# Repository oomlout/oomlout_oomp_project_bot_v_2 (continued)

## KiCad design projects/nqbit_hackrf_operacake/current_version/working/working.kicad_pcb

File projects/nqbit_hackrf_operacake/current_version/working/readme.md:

# hackrf
 
## summary 
* id: nqbit_hackrf_operacake
* user: nqbit
* name: hackrf
* board: operacake
* repo: https://github.com/nqbit/hackrf
* src_file_repo_kicad_pcb: hardware/operacake/operacake.kicad_pcb
* src_file_repo_kicad_pcb_link: https://github.com/nqbit/hackrf/tree/master/hardware/operacake/operacake.kicad_pcb

* src_file_repo_sch: hardware/operacake/operacake.sch
* src_file_repo_sch_link: https://github.com/nqbit/hackrf/tree/master/hardware/operacake/operacake.sch
* full details link: https://github.com/oomlout/oomlout_oomp_project_bot_v_2/tree/main/projects/nqbit_hackrf_operacake/current_version/working

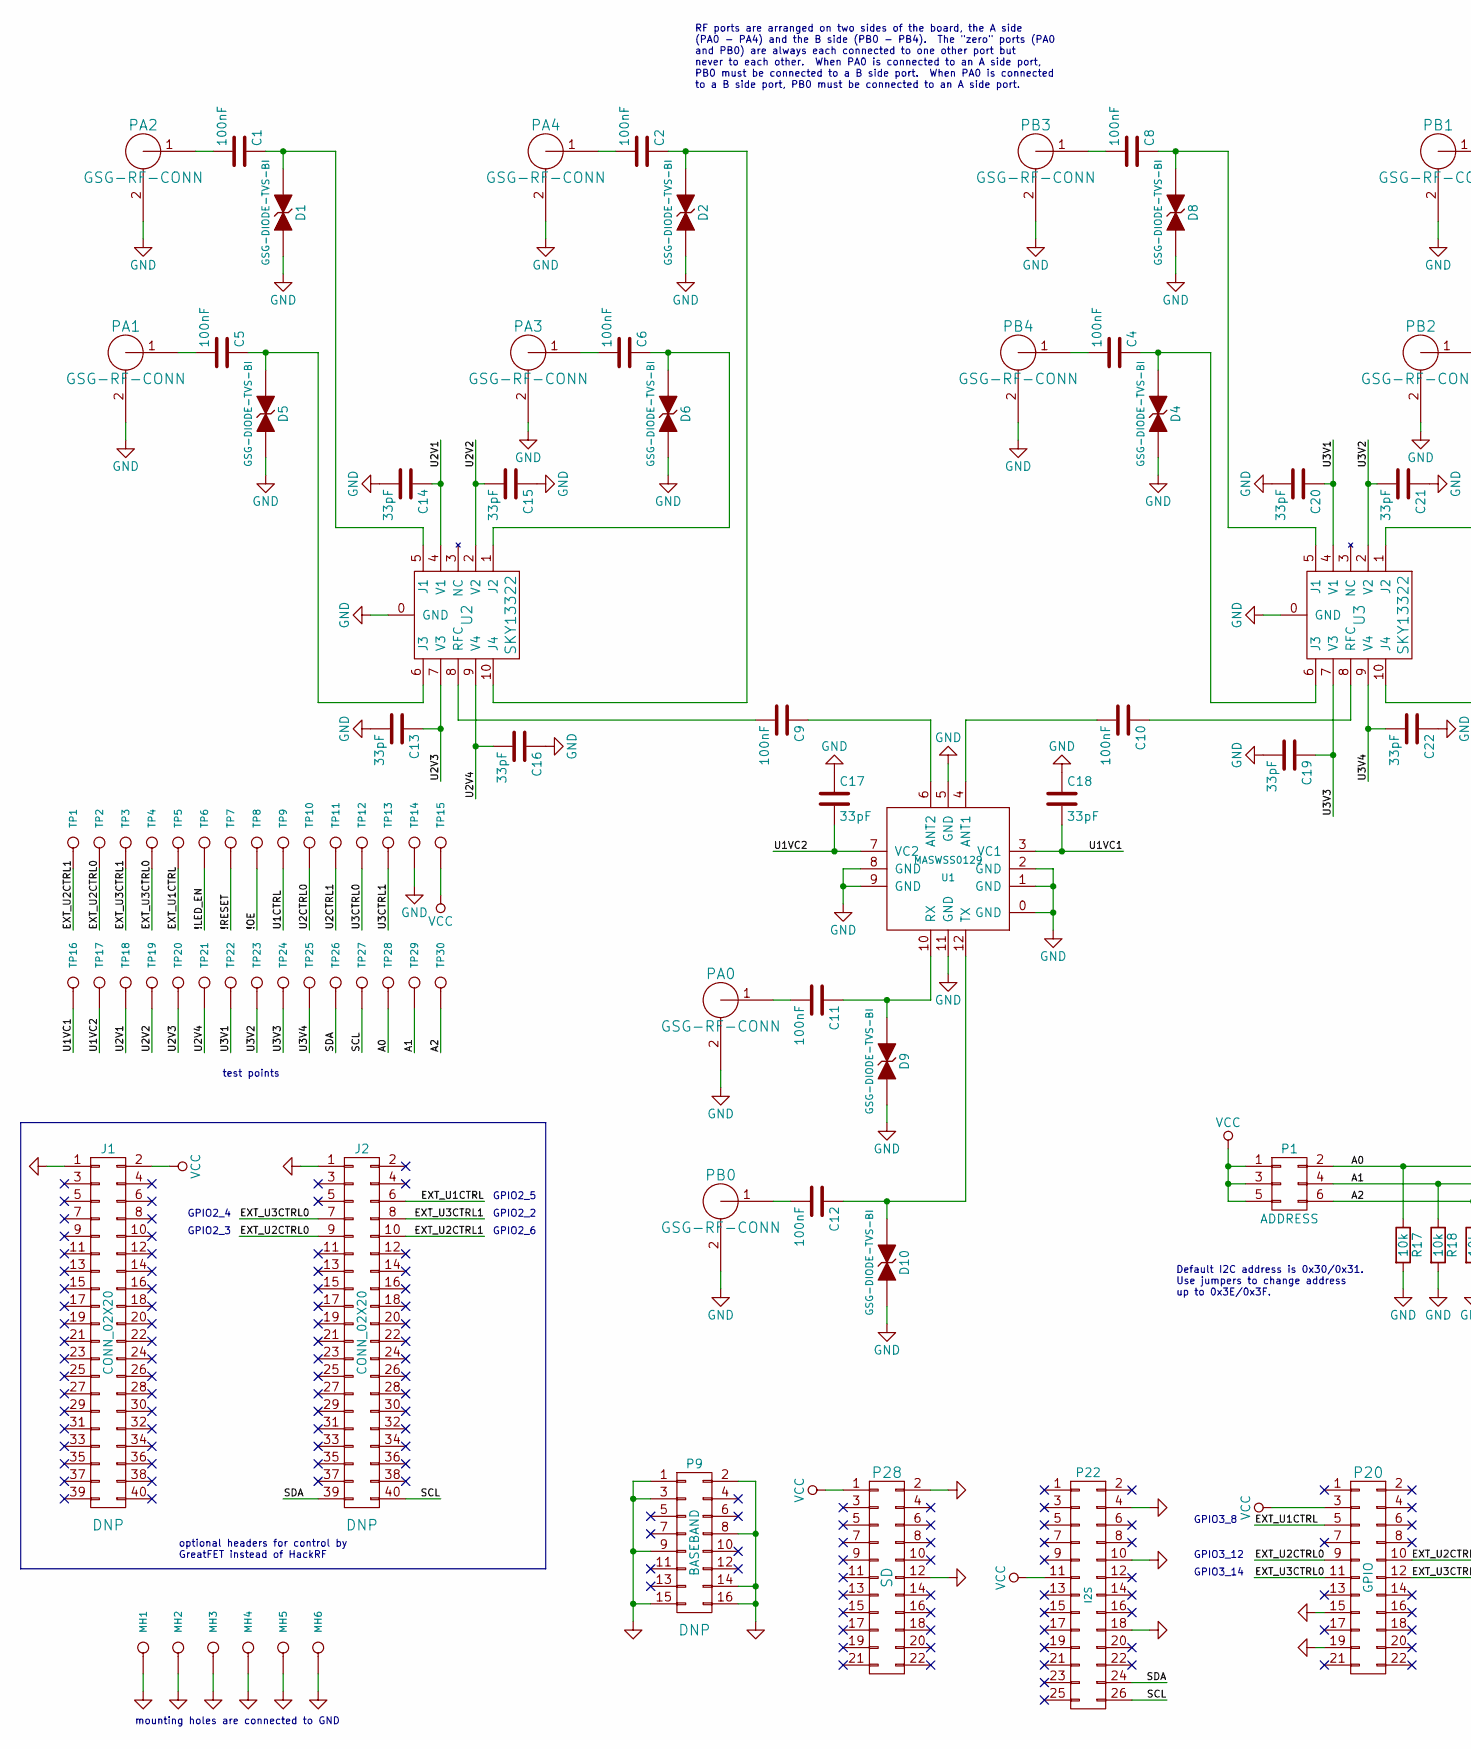
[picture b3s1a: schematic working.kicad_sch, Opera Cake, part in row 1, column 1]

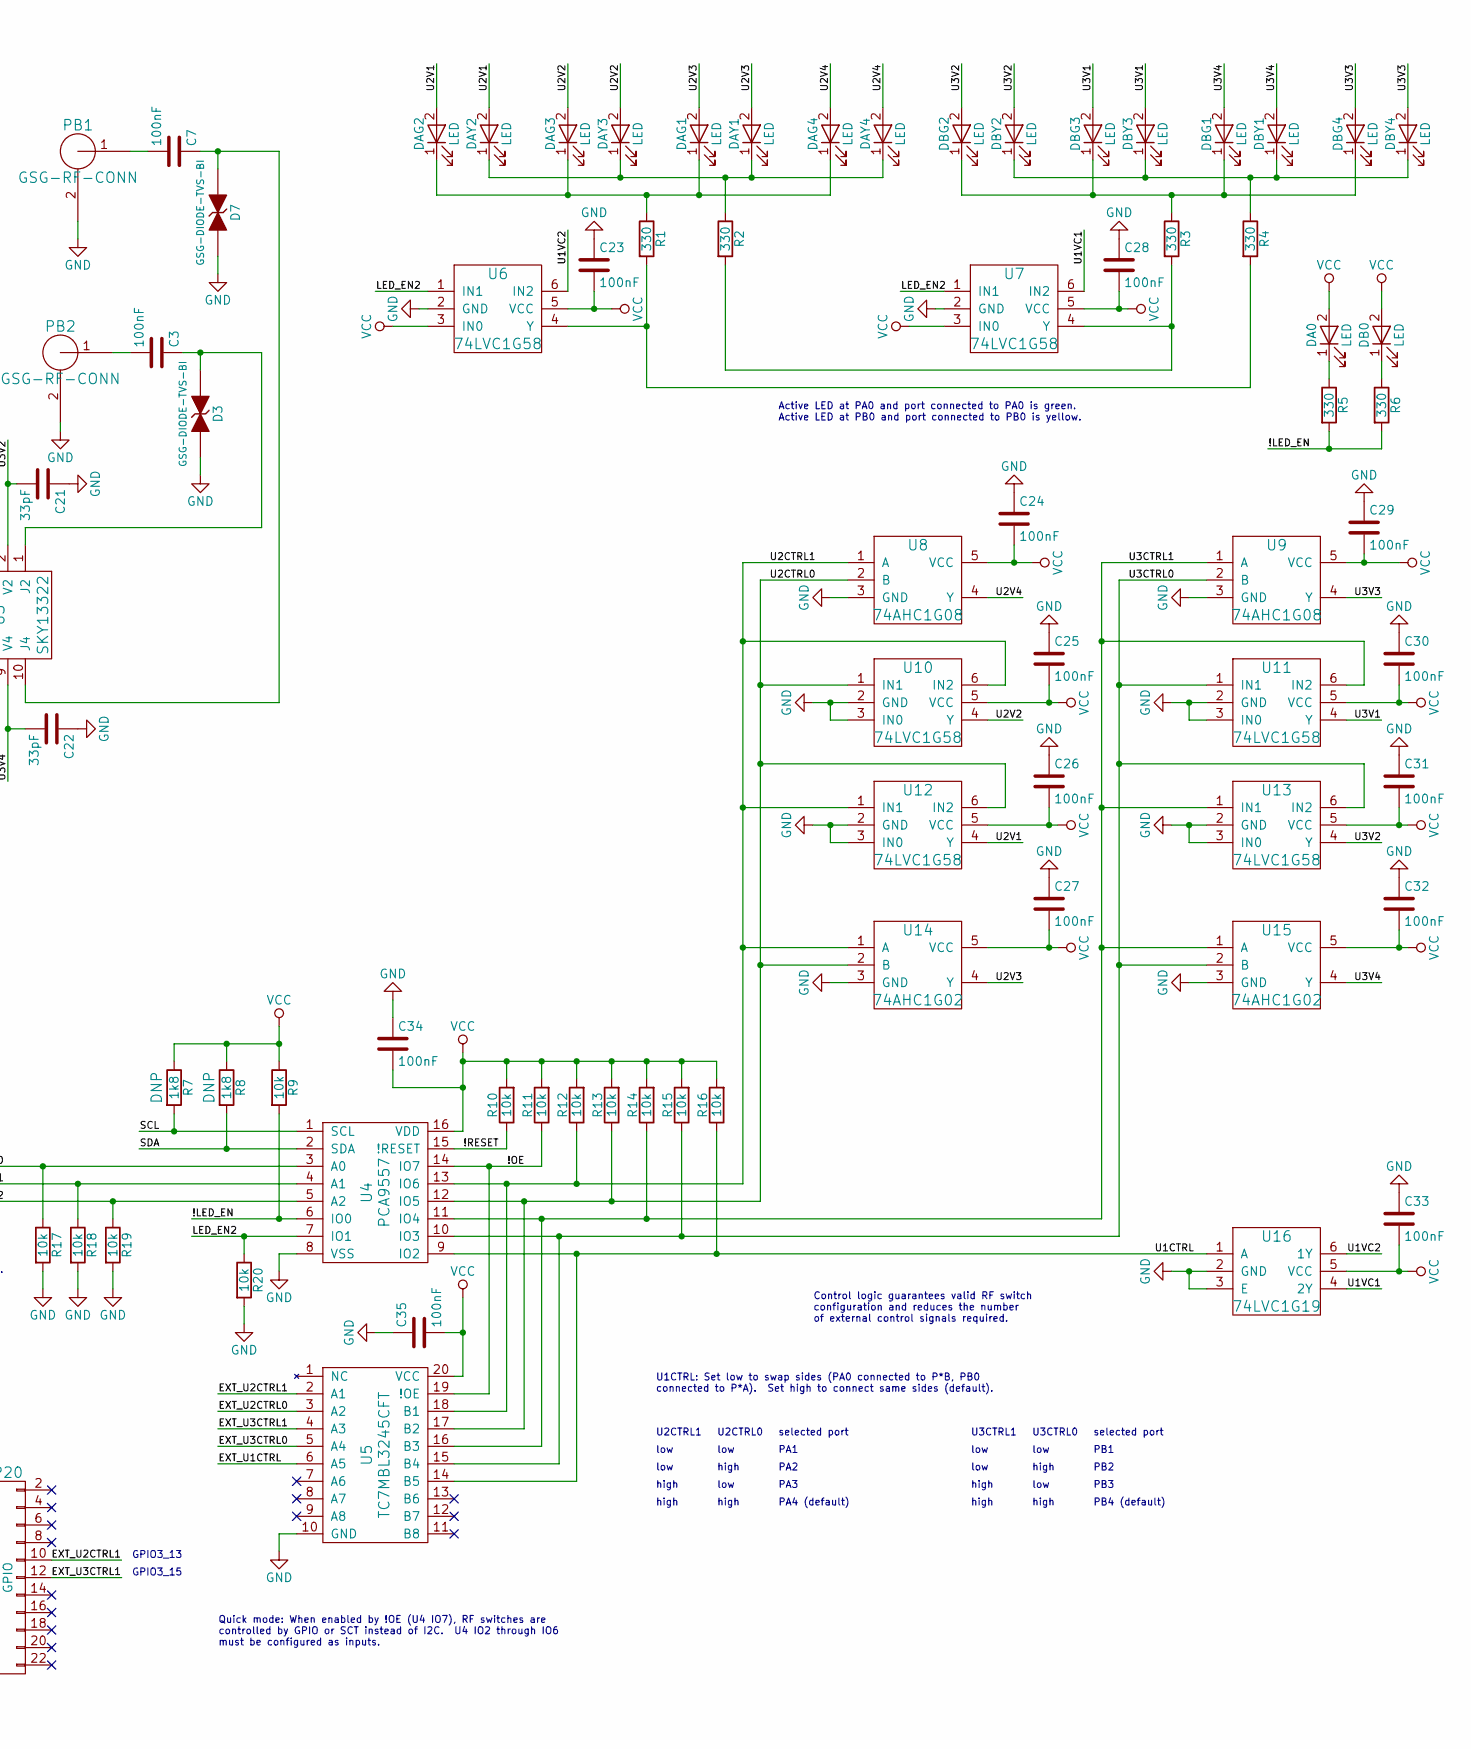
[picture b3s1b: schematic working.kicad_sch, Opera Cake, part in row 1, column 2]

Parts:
C1, C2, C3, C4, C5, C6, C7, C8, C9, C10, C11, C12, C23, C24, C25, C26, C27, C28, C29, C30, C31, C32, C33, C34, C35: 100nF; 0402; Part Number GRM155R61A104KA01D
C13, C14, C15, C16, C17, C18, C19, C20, C21, C22: 33pF; 0402; Part Number GRM1555C1H330JA01D
D1, D2, D3, D4, D5, D6, D7, D8, D9, D10: GSG-DIODE-TVS-BI; 0402; Part Number LXES15AAA1-153
DA0: LED; 0603D; Part Number SML-LX0603GW-TR
DAG1, DAG2, DAG3, DAG4: LED; 0603D; Part Number SML-LX0603GW-TR
DAY1, DAY2, DAY3, DAY4: LED; 0603D; Part Number SML-LX0603YW-TR
DB0: LED; 0603D; Part Number SML-LX0603YW-TR
DBG1, DBG2, DBG3, DBG4: LED; 0603D; Part Number SML-LX0603GW-TR
DBY1, DBY2, DBY3, DBY4: LED; 0603D; Part Number SML-LX0603YW-TR
J1, J2: CONN_02X20; HEADER-2x20-REVERSE
MH1, MH2, MH3, MH4, MH5, MH6: MOUNTING_HOLE; HOLE126MIL-COPPER
P1: ADDRESS; HEADER-2x3; Part Number XG8T-0631
P9: BASEBAND; HEADER-2x8; Part Number SSQ-108-03-G-D
P20: GPIO; HEADER-2x11; Part Number SSQ-111-03-G-D
P22: I2S; HEADER-2x13; Part Number SSQ-113-03-G-D
P28: SD; HEADER-2x11; Part Number SSQ-111-03-G-D
PA0, PA1, PA2, PA3, PA4: GSG-RF-CONN; GSG-SMA-73251-2120; Part Number 73251-2121
PB0, PB1, PB2, PB3, PB4: GSG-RF-CONN; GSG-SMA-73251-2120; Part Number 73251-2121
R1, R2, R3, R4, R5, R6: 330; 0603; Part Number RMCF0603JT330R
R7, R8: 1k8; 0603
R9, R10, R11, R12, R13, R14, R15, R16, R17, R18, R19, R20: 10k; 0603; Part Number ERJ-3GEYJ103V
TP1, TP2, TP3, TP4, TP5, TP6, TP7, TP8, TP9, TP10, TP11, TP12, TP13, TP14, TP15, TP16, TP17, TP18, TP19, TP20, TP21, TP22, TP23, TP24, TP25, TP26, TP27, TP28, TP29, TP30: CONN_1; TESTPOINT-50MIL
U1: MASWSS0129; QFN12-3; Part Number MASWSS0129TR-3000
U2, U3: SKY13322; SKY13322-375LF; Part Number SKY13322-375LF
U4: PCA9557; TSSOP16; Part Number PCA9557PW,118
U5: TC7MBL3245CFT; TSSOP20; Part Number TC7MBL3245CFT(EL)
U6, U7, U10, U11, U12, U13: 74LVC1G58; SOT363; Part Number 74LVC1G58DW-7
U8, U9: 74AHC1G08; SOT353-1; Part Number 74AHC1G08SE-7
U14, U15: 74AHC1G02; SOT353-1; Part Number 74AHC1G02SE-7
U16: 74LVC1G19; SOT363; Part Number 74LVC1G19GW,125

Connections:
/!LED_EN: R5.2, R6.2, R9.2, TP6.1, U4.6 (IO0)
/!OE: R11.1, TP8.1, U4.14 (IO7), U5.19 (!OE)
/!RESET: R10.1, TP7.1, U4.15 (!RESET)
/A0: P1.2, R17.1, TP28.1, U4.3 (A0)
/A1: P1.4, R18.1, TP29.1, U4.4 (A1)
/A2: P1.6, R19.1, TP30.1, U4.5 (A2)
/EXT_U1CTRL: J2.6, P20.5, TP5.1, U5.6 (A5)
/EXT_U2CTRL0: J2.9, P20.9, TP2.1, U5.3 (A2)
/EXT_U2CTRL1: J2.10, P20.10, TP1.1, U5.2 (A1)
/EXT_U3CTRL0: J2.7, P20.11, TP4.1, U5.5 (A4)
/EXT_U3CTRL1: J2.8, P20.12, TP3.1, U5.4 (A3)
/LED_EN2: R20.1, U4.7 (IO1), U6.1 (IN1), U7.1 (IN1)
/SCL: J2.40, P22.26, R7.2, TP27.1, U4.1 (SCL)
/SDA: J2.39, P22.24, R8.2, TP26.1, U4.2 (SDA)
/U1CTRL: R16.1, TP9.1, U4.9 (IO2), U5.14 (B5), U16.1 (A)
/U1VC1: C18.2, TP16.1, U1.3 (VC1), U7.6 (IN2), U16.4 (2Y)
/U1VC2: C17.2, TP17.1, U1.7 (VC2), U6.6 (IN2), U16.6 (1Y)
/U2CTRL0: R13.1, TP10.1, U4.12 (IO5), U5.17 (B2), U8.2 (B), U10.1 (IN1), U12.6 (IN2), U14.2 (B)
/U2CTRL1: R12.1, TP11.1, U4.13 (IO6), U5.18 (B1), U8.1 (A), U10.6 (IN2), U12.1 (IN1), U14.1 (A)
/U2V1: C14.1, DAG2.2 (A), DAY2.2 (A), TP18.1, U2.4 (V1), U12.4 (Y)
/U2V2: C15.2, DAG3.2 (A), DAY3.2 (A), TP19.1, U2.2 (V2), U10.4 (Y)
/U2V3: C13.1, DAG1.2 (A), DAY1.2 (A), TP20.1, U2.7 (V3), U14.4 (Y)
/U2V4: C16.2, DAG4.2 (A), DAY4.2 (A), TP21.1, U2.9 (V4), U8.4 (Y)
/U3CTRL0: R15.1, TP12.1, U4.10 (IO3), U5.15 (B4), U9.2 (B), U11.1 (IN1), U13.6 (IN2), U15.2 (B)
/U3CTRL1: R14.1, TP13.1, U4.11 (IO4), U5.16 (B3), U9.1 (A), U11.6 (IN2), U13.1 (IN1), U15.1 (A)
/U3V1: C20.1, DBG3.2 (A), DBY3.2 (A), TP22.1, U3.4 (V1), U11.4 (Y)
/U3V2: C21.2, DBG2.2 (A), DBY2.2 (A), TP23.1, U3.2 (V2), U13.4 (Y)
/U3V3: C19.1, DBG4.2 (A), DBY4.2 (A), TP24.1, U3.7 (V3), U9.4 (Y)
/U3V4: C22.2, DBG1.2 (A), DBY1.2 (A), TP25.1, U3.9 (V4), U15.4 (Y)
GND: C13.2, C14.2, C15.1, C16.1, C17.1, C18.1, C19.2, C20.2, C21.1, C22.1, C23.1, C24.1, C25.1, C26.1, C27.1, C28.1, C29.1, C30.1, C31.1, C32.1, C33.1, C34.1, C35.1, D1.2 (K), D2.2 (K), D3.2 (K), D4.2 (K), D5.2 (K), D6.2 (K), D7.2 (K), D8.2 (K), D9.2 (K), D10.2 (K), J1.1, J2.1, MH1.1, MH2.1, MH3.1, MH4.1, MH5.1, MH6.1, P9.1, P9.2, P9.3, P9.8, P9.9, P9.14, P9.15, P9.16, P20.15, P20.19, P22.4, P22.10, P22.18, P28.2, P28.12, PA0.2 (GND), PA1.2 (GND), PA2.2 (GND), PA3.2 (GND), PA4.2 (GND), PB0.2 (GND), PB1.2 (GND), PB2.2 (GND), PB3.2 (GND), PB4.2 (GND), R17.2, R18.2, R19.2, R20.2, TP14.1, U1.0 (GND), U1.1 (GND), U1.2 (GND), U1.5 (GND), U1.8 (GND), U1.9 (GND), U1.11 (GND), U2.0 (GND), U3.0 (GND), U4.8 (VSS), U5.10 (GND), U6.2 (GND), U7.2 (GND), U8.3 (GND), U9.3 (GND), U10.2 (GND), U10.3 (IN0), U11.2 (GND), U11.3 (IN0), U12.2 (GND), U12.3 (IN0), U13.2 (GND), U13.3 (IN0), U14.3 (GND), U15.3 (GND), U16.2 (GND), U16.3 (E)
unnamed: C1.1, D1.1 (A), U2.5 (J1)
unnamed: C1.2, PA2.1 (RF)
unnamed: C2.1, D2.1 (A), U2.10 (J4)
unnamed: C2.2, PA4.1 (RF)
unnamed: C3.1, D3.1 (A), U3.1 (J2)
unnamed: C3.2, PB2.1 (RF)
unnamed: C4.1, D4.1 (A), U3.6 (J3)
unnamed: C4.2, PB4.1 (RF)
unnamed: C5.1, D5.1 (A), U2.6 (J3)
unnamed: C5.2, PA1.1 (RF)
unnamed: C6.1, D6.1 (A), U2.1 (J2)
unnamed: C6.2, PA3.1 (RF)
unnamed: C7.1, D7.1 (A), U3.10 (J4)
unnamed: C7.2, PB1.1 (RF)
unnamed: C8.1, D8.1 (A), U3.5 (J1)
unnamed: C8.2, PB3.1 (RF)
unnamed: C9.1, U1.6 (ANT2)
unnamed: C9.2, U2.8 (RFC)
unnamed: C10.1, U3.8 (RFC)
unnamed: C10.2, U1.4 (ANT1)
unnamed: C11.1, D9.1 (A), U1.10 (RX)
unnamed: C11.2, PA0.1 (RF)
unnamed: C12.1, D10.1 (A), U1.12 (TX)
unnamed: C12.2, PB0.1 (RF)
unnamed: DA0.1 (K), R5.1
unnamed: DAG1.1 (K), DAG2.1 (K), DAG3.1 (K), DAG4.1 (K), R1.1
unnamed: DAY1.1 (K), DAY2.1 (K), DAY3.1 (K), DAY4.1 (K), R2.1
unnamed: DB0.1 (K), R6.1
unnamed: DBG1.1 (K), DBG2.1 (K), DBG3.1 (K), DBG4.1 (K), R3.1
unnamed: DBY1.1 (K), DBY2.1 (K), DBY3.1 (K), DBY4.1 (K), R4.1
unnamed: R1.2, R4.2, U6.4 (Y)
unnamed: R2.2, R3.2, U7.4 (Y)
VCC: C23.2, C24.2, C25.2, C26.2, C27.2, C28.2, C29.2, C30.2, C31.2, C32.2, C33.2, C34.2, C35.2, DA0.2 (A), DB0.2 (A), J1.2, P1.1, P1.3, P1.5, P20.3, P22.11, P28.1, R7.1, R8.1, R9.1, R10.2, R11.2, R12.2, R13.2, R14.2, R15.2, R16.2, TP15.1, U4.16 (VDD), U5.20 (VCC), U6.3 (IN0), U6.5 (VCC), U7.3 (IN0), U7.5 (VCC), U8.5 (VCC), U9.5 (VCC), U10.5 (VCC), U11.5 (VCC), U12.5 (VCC), U13.5 (VCC), U14.5 (VCC), U15.5 (VCC), U16.5 (VCC)

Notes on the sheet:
high
RF ports are arranged on two sides of the board, the A side (PA0 - PA4) and the B side (PB0 - PB4). The "zero" ports (PA0 and PB0) are always each connected to one other port but never to each other. When PA0 is connected to an A side port, PB0 must be connected to a B side port. When PA0 is connec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
Active LED at PA0 and port connected to PA0 is green. Active LED at PB0 and port connected to PB0 is yellow.
PB2
low
GPIO2_5
U2CTRL0
selected port
GPIO2_3
PA2
GPIO3_8
PA1
test points
GPIO2_6
Quick mode: When enabled by !OE (U4 IO7), RF switches are controlled by GPIO or SCT instead of I2C. U4 IO2 through IO6 must be configured as inputs.
U3CTRL1
GPIO3_15
mounting holes are connected to GND
optional headers for control by GreatFET instead of HackRF
U3CTRL0
GPIO3_13
GPIO3_14
Control logic guarantees valid RF switch configuration and reduces the number of external control signals required.
PB4 (default)
PB3
Default I2C address is 0x30/0x31. Use jumpers to change address up to 0x3E/0x3F.
U2CTRL1
PA4 (default)
GPIO3_12
U1CTRL: Set low to swap sides (PA0 connected to P*B, PB0 connected to P*A). Set high to connect same sides (default).
GPIO2_2
PB1
GPIO2_4
PA3

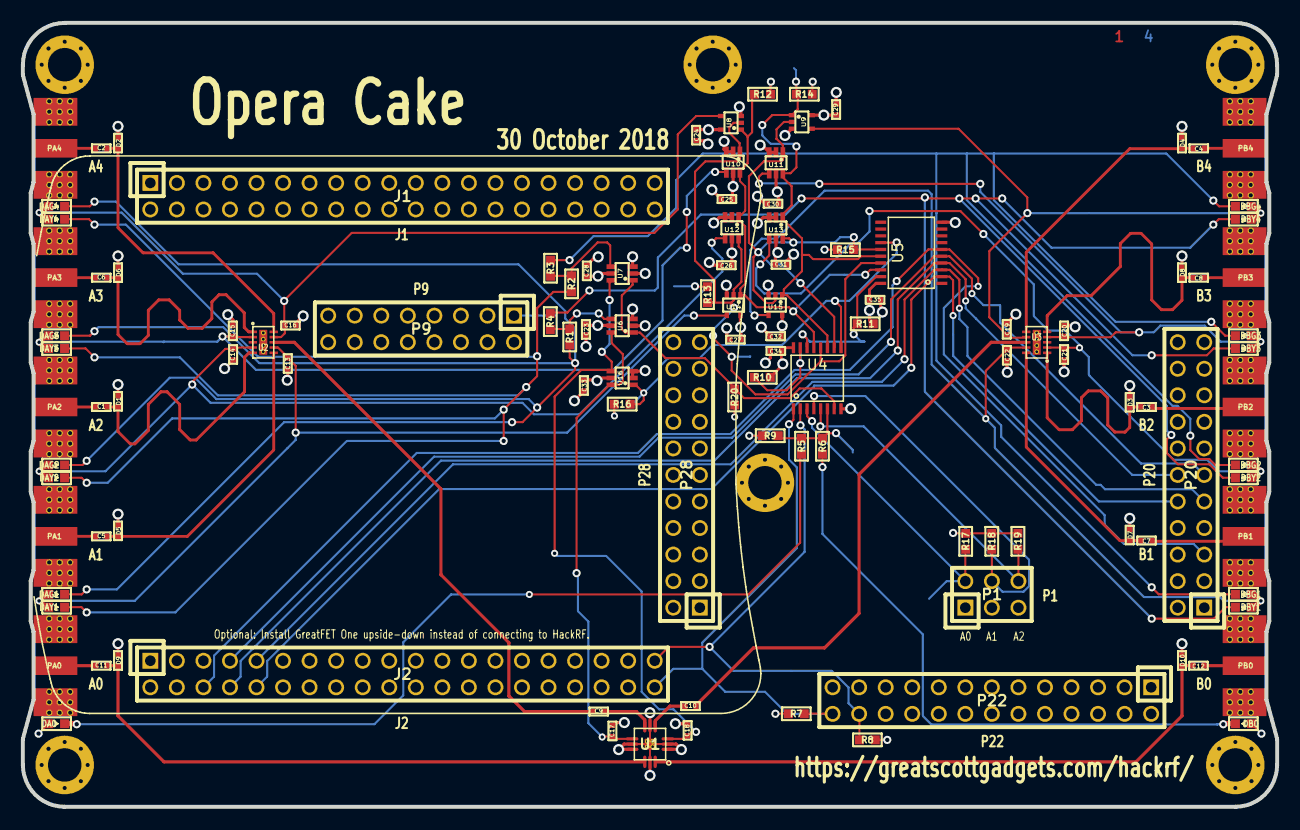
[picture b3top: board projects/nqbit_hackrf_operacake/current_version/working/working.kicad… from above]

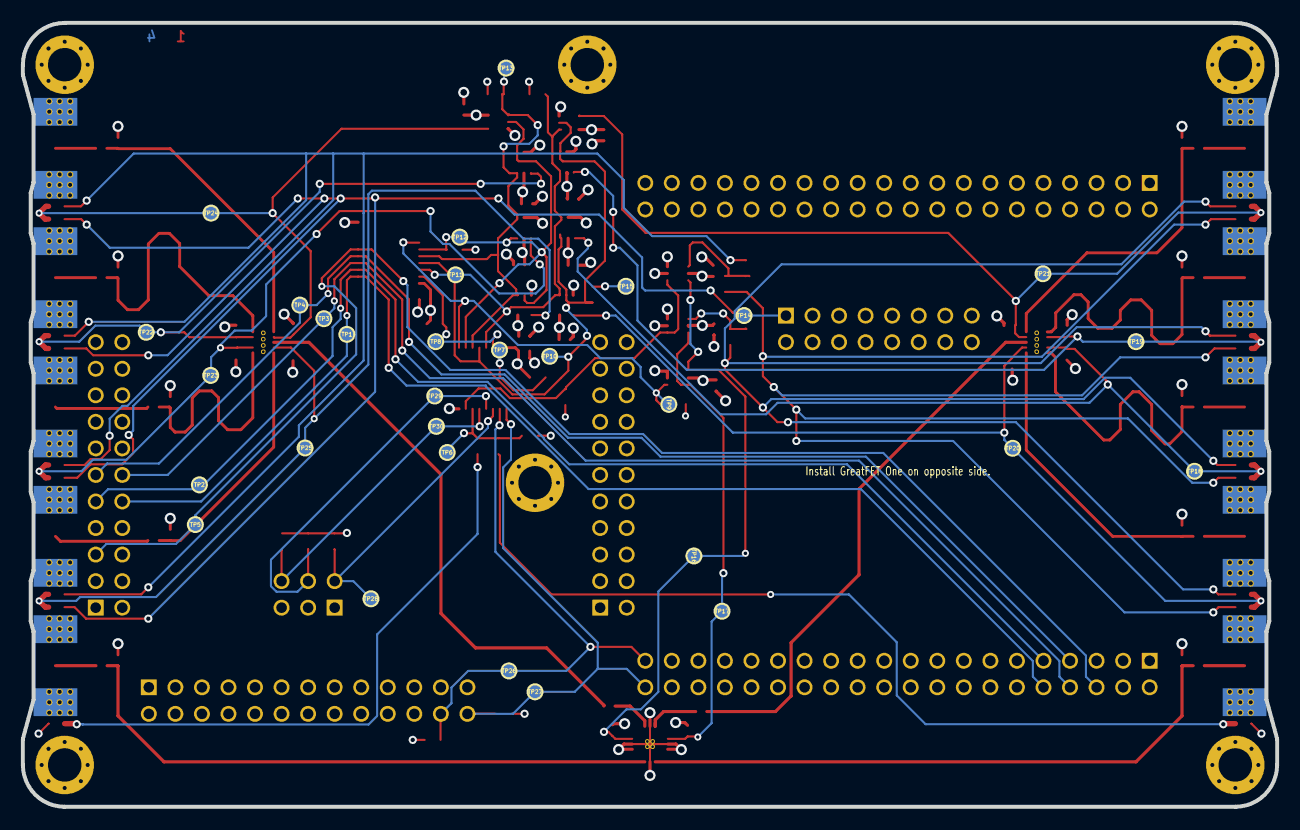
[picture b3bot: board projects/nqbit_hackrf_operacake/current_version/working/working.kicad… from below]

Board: 4 copper layers, 120.0 x 75.0 mm, 152 parts (30 on the bottom side), 63 nets.

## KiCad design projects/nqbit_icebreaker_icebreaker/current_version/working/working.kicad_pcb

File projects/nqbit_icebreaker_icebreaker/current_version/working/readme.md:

# icebreaker
 
## summary 
* id: nqbit_icebreaker_icebreaker
* user: nqbit
* name: icebreaker
* board: icebreaker
* repo: https://github.com/nqbit/icebreaker
* src_file_repo_kicad_pcb: hardware/v1.0e/icebreaker.kicad_pcb
* src_file_repo_kicad_pcb_link: https://github.com/nqbit/icebreaker/tree/master/hardware/v1.0e/icebreaker.kicad_pcb

* src_file_repo_sch: hardware/v1.0e/icebreaker.sch
* src_file_repo_sch_link: https://github.com/nqbit/icebreaker/tree/master/hardware/v1.0e/icebreaker.sch
* full details link: https://github.com/oomlout/oomlout_oomp_project_bot_v_2/tree/main/projects/nqbit_icebreaker_icebreaker/current_version/working

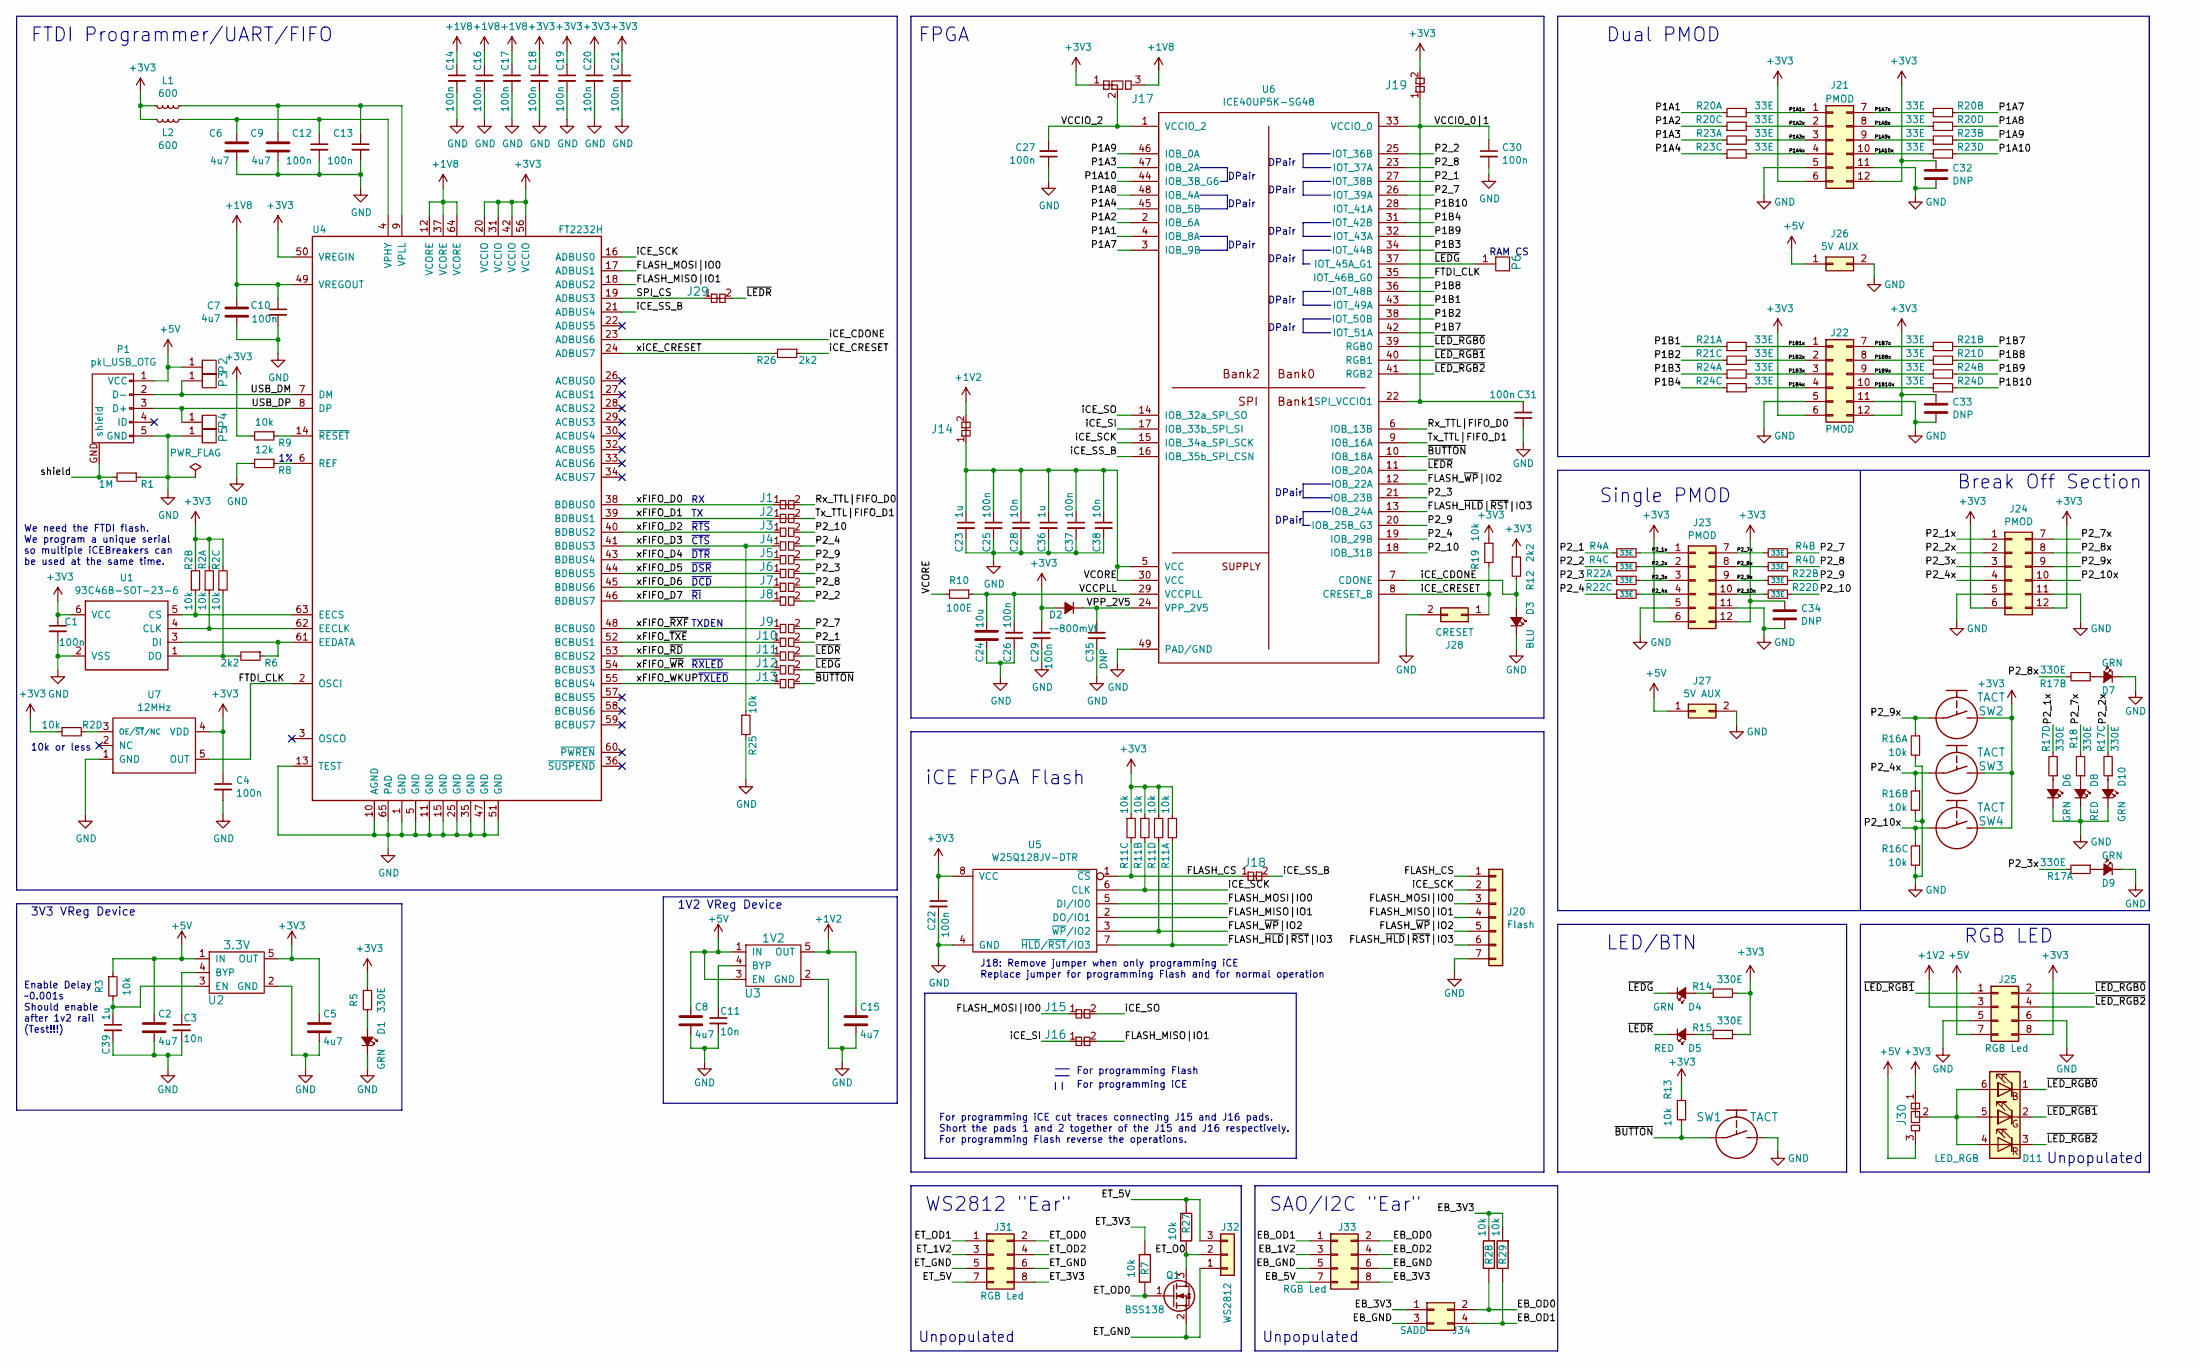
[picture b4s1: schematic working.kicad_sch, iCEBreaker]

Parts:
C1, C4, C10, C12, C13, C14, C16, C17, C18, C19, C20, C21, C22, C25, C26, C27, C29, C30, C31, C37: 100n; C_0402
C2, C5, C6, C7, C8, C9, C15: 4u7; C_0603
C3, C11, C28, C38: 10n; C_0402
C23, C36, C39: 1u; C_0402
C24: 10u; C_0603
C32, C33, C34: DNP; C_0603
C35: DNP; C_0402
D1, D4, D6, D7, D9, D10: GRN; D_0603
D2: ~~800mVf; D_SOD-523
D3: BLU; D_0603
D5, D8: RED; D_0603
D11: LED_RGB; LED_Cree_PLCC6_3.4x3.4mm
J1, J2, J15, J16, J18, J29: Jumper; J_NC_0603_15
J3, J4, J5, J6, J7, J8, J9, J10, J11, J12, J13: Jumper; J_0603
J14, J19: Jumper; J_NC_0603_30
J17, J30: Jumper; J_NCNO_0903_30
J20: Flash; Pin_Header_Straight_1x07
J21, J22: PMOD; Socket_Strip_Angled_2x06
J23: PMOD; Socket_Strip_Straight_2x06
J24: PMOD; Pin_Header_Straight_2x06
J25: RGB Led; Pin_Header_Straight_2x04
J26, J27: 5V AUX; Pin_Header_Straight_2x01
J28: CRESET; PinHeader_2x01_P2.54mm_Vertical
J31, J33: RGB Led; PinSocket_2x04_P2.54mm_Vertical
J32: WS2812; PinHeader_1x03_P2.54mm_Vertical
J34: SADD; PinSocket_2x02_P2.54mm_Vertical
L1, L2: 600; L_0402
P1: pkl_USB_OTG; Connector_USB_Micro_B_SMD
P2, P3, P4, P5: UP; PAD_SMD_1x2.65
P6: RAM_CS; PAD_SMD_1x1.5
Q1: BSS138; SOT-23
R1: 1M; R_0402
R2, R11, R16: 10k; R_Array_Convex_4x0402
R3, R9, R13, R19, R25: 10k; R_0402
R4, R20, R21, R22, R23, R24: 33E; R_Array_Convex_4x0402
R5, R14, R15, R18: 330E; R_0402
R6, R12, R26: 2k2; R_0402
R7, R27, R28, R29: 10k; R_0603
R8: 12k; R_0402
R10: 100E; R_0402
R17: 330E; R_Array_Convex_4x0402
SW1, SW2, SW3, SW4: TACT; SW_SPST_3x4x2.5
U1: 93C46B-SOT-23-6; SOT-23-6
U2: 3.3V; SOT-23-5
U3: 1V2; SOT-23-5
U4: FT2232H; QFN-64-4.45mm1EP_9x9mm_Pitch0.5mm
U5: W25Q128JV-DTR; SOIC-8_5.3x5.3mm_Pitch1.27mm
U6: ICE40UP5K-SG48; QFN-48-1EP_7x7mm_Pitch0.5mm
U7: 12MHz; SOT-23-5

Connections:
+1V2: C15.1, J14.2, J25.3, U3.5 (OUT)
+1V8: C7.1, C10.1, C14.1, C16.1, C17.1, J17.3, U4.12 (VCORE), U4.37 (VCORE), U4.49 (VREGOUT), U4.64 (VCORE)
+3V3: C1.1, C4.1, C5.1, C18.1, C19.1, C20.1, C21.1, C22.1, C29.1, C32.2, C33.2, C34.2, D2.A, J17.1, J19.2, J21.6, J21.12, J22.6, J22.12, J23.6, J23.12, J24.6, J24.12, J25.8, J30.1, L1.1, L2.1, R2.2, R2.4, R2.6, R2.7, R5.1, R9.2, R11.1, R11.3, R11.5, R11.7, R12.1, R13.2, R14.2, R15.2, R19.1, SW2.2, SW3.2, SW4.2, U1.6 (VCC), U2.5 (OUT), U4.20 (VCCIO), U4.31 (VCCIO), U4.42 (VCCIO), U4.50 (VREGIN), U4.56 (VCCIO), U5.8 (VCC), U7.4 (VDD)
+5V: C2.1, C8.1, J25.7, J26.1, J27.1, J30.3, P1.1 (VCC), P2.1, R3.1, U2.1 (IN), U3.1 (IN), U3.3 (EN)
/EB_3V3: J33.8, J34.1, R28.2, R29.2
/EB_GND: J33.5, J33.6, J34.3
/EB_OD0: J33.2, J34.2, R28.1
/EB_OD1: J33.1, J34.4, R29.1
/ET_3V3: J31.8, R7.1
/ET_5V: J31.7, J32.3, R27.1
/ET_GND: J31.5, J31.6, J32.1, Q1.2 (S)
/ET_O0: J32.2, Q1.3 (D), R27.2
/ET_OD0: J31.2, Q1.1 (G), R7.2
/FLASH_CS: J18.1, J20.1, R11.6, U5.1 (~CS)
/FLASH_MISO|IO1: J16.2, J20.4, U4.18 (ADBUS2), U5.2 (DO/IO1)
/FLASH_MOSI|IO0: J15.1, J20.3, U4.17 (ADBUS1), U5.5 (DI/IO0)
/FLASH_~HLD|~RST|IO3: J20.6, R11.2, U5.7 (~HLD/~RST/IO3), U6.13 (IOB_24A)
/FLASH_~WP|IO2: J20.5, R11.8, U5.3 (~WP/IO2), U6.12 (IOB_22A)
/FTDI_CLK: U4.2 (OSCI), U6.35 (IOT_46B_G0), U7.5 (OUT)
/P1A1: R20.1, U6.4 (IOB_8A)
/P1A1x: J21.1, R20.2
/P1A2: R20.5, U6.2 (IOB_6A)
/P1A2x: J21.2, R20.6
/P1A3: R23.1, U6.47 (IOB_2A)
/P1A3x: J21.3, R23.2
/P1A4: R23.5, U6.45 (IOB_5B)
/P1A4x: J21.4, R23.6
/P1A7: R20.3, U6.3 (IOB_9B)
/P1A7x: J21.7, R20.4
/P1A8: R20.7, U6.48 (IOB_4A)
/P1A8x: J21.8, R20.8
/P1A9: R23.3, U6.46 (IOB_0A)
/P1A9x: J21.9, R23.4
/P1A10: R23.7, U6.44 (IOB_3B_G6)
/P1A10x: J21.10, R23.8
/P1B1: R21.1, U6.43 (IOT_49A)
/P1B1x: J22.1, R21.2
/P1B2: R21.5, U6.38 (IOT_50B)
/P1B2x: J22.2, R21.6
/P1B3: R24.1, U6.34 (IOT_44B)
/P1B3x: J22.3, R24.2
/P1B4: R24.5, U6.31 (IOT_42B)
/P1B4x: J22.4, R24.6
/P1B7: R21.3, U6.42 (IOT_51A)
/P1B7x: J22.7, R21.4
/P1B8: R21.7, U6.36 (IOT_48B)
/P1B8x: J22.8, R21.8
/P1B9: R24.3, U6.32 (IOT_43A)
/P1B9x: J22.9, R24.4
/P1B10: R24.7, U6.28 (IOT_41A)
/P1B10x: J22.10, R24.8
/P2_1: J10.2, R4.1, U6.27 (IOT_38B)
/P2_1x: J23.1, J24.1, R4.2, R17.8
/P2_2: J8.2, R4.5, U6.25 (IOT_36B)
/P2_2x: J23.2, J24.2, R4.6, R17.6
/P2_3: J6.2, R22.1, U6.21 (IOB_23B)
/P2_3x: J23.3, J24.3, R17.2, R22.2
/P2_4: J4.2, R22.5, U6.19 (IOB_29B)
/P2_4x: J23.4, J24.4, R16.3, R22.6, SW3.1
/P2_7: J9.2, R4.3, U6.26 (IOT_39A)
/P2_7x: J23.7, J24.7, R4.4, R18.2
/P2_8: J7.2, R4.7, U6.23 (IOT_37A)
/P2_8x: J23.8, J24.8, R4.8, R17.4
/P2_9: J5.2, R22.3, U6.20 (IOB_25B_G3)
/P2_9x: J23.9, J24.9, R16.1, R22.4, SW2.1
/P2_10: J3.2, R22.7, U6.18 (IOB_31B)
/P2_10x: J23.10, J24.10, R16.5, R22.8, SW4.1
/Rx_TTL|FIFO_D0: J1.2, U6.6 (IOB_13B)
/SPI_CS: J29.1, U4.19 (ADBUS3)
/Tx_TTL|FIFO_D1: J2.2, U6.9 (IOB_16A)
/USB_DM: P1.2 (D-), P3.1, U4.7 (DM)
/USB_DP: P1.3 (D+), P4.1, U4.8 (DP)
/VCCIO_0|1: C30.1, C31.1, J19.1, U6.22 (SPI_VCCIO1), U6.33 (VCCIO_0)
/VCCIO_2: C27.2, J17.2, U6.1 (VCCIO_2)
/VCCPLL: C24.1, C26.1, R10.1, U6.29 (VCCPLL)
/VCORE: C23.1, C25.1, C28.1, C36.1, C37.1, C38.1, J14.1, R10.2, U6.5 (VCC), U6.30 (VCC)
/VPP_2V5: C35.1, D2.C, U6.24 (VPP_2V5)
/iCE_CDONE: D3.A, R12.2, U4.23 (ADBUS6), U6.7 (CDONE)
/iCE_CRESET: J28.1, R19.2, R26.1, U6.8 (CRESET_B)
/iCE_SCK: J20.2, R11.4, U4.16 (ADBUS0), U5.6 (CLK), U6.15 (IOB_34a_SPI_SCK)
/iCE_SI: J16.1, U6.17 (IOB_33b_SPI_SI)
/iCE_SO: J15.2, U6.14 (IOB_32a_SPI_SO)
/iCE_SS_B: J18.2, U4.21 (ADBUS4), U6.16 (IOB_35b_SPI_CSN)
/shield: P1.GND (shield), R1.2
/xFIFO_D0: J1.1, U4.38 (BDBUS0)
/xFIFO_D1: J2.1, U4.39 (BDBUS1)
/xFIFO_D2: J3.1, U4.40 (BDBUS2)
/xFIFO_D3: J4.1, R25.1, U4.41 (BDBUS3)
/xFIFO_D4: J5.1, U4.43 (BDBUS4)
/xFIFO_D5: J6.1, U4.44 (BDBUS5)
/xFIFO_D6: J7.1, U4.45 (BDBUS6)
/xFIFO_D7: J8.1, U4.46 (BDBUS7)
/xFIFO_WKUP: J13.1, U4.55 (BCBUS4)
/xFIFO_~RD: J11.1, U4.53 (BCBUS2)
/xFIFO_~RXF: J9.1, U4.48 (BCBUS0)
/xFIFO_~TXE: J10.1, U4.52 (BCBUS1)
/xFIFO_~WR: J12.1, U4.54 (BCBUS3)
/xiCE_CRESET: R26.2, U4.24 (ADBUS7)
/~BUTTON: J13.2, R13.1, SW1.1, U6.10 (IOB_18A)
/~LEDG: D4.C, J12.2, P6.1, U6.37 (IOT_45A_G1)
/~LEDR: D5.C, J11.2, J29.2, U6.11 (IOB_20A)
/~LED_RGB0: D11.1 (RK), J25.2, U6.39 (RGB0)
/~LED_RGB1: D11.2 (GK), J25.1, U6.40 (RGB1)
/~LED_RGB2: D11.3 (BK), J25.4, U6.41 (RGB2)
GND: C1.2, C2.2, C3.2, C4.2, C5.2, C6.2, C7.2, C8.2, C9.2, C10.2, C11.2, C12.2, C13.2, C14.2, C15.2, C16.2, C17.2, C18.2, C19.2, C20.2, C21.2, C22.2, C23.2, C24.2, C25.2, C26.2, C27.1, C28.2, C29.2, C30.2, C31.2, C32.1, C33.1, C34.1, C35.2, C36.2, C37.2, C38.2, C39.2, D1.C, D3.C, D6.C, D7.C, D8.C, D9.C, D10.C, J20.7, J21.5, J21.11, J22.5, J22.11, J23.5, J23.11, J24.5, J24.11, J25.5, J25.6, J26.2, J27.2, J28.2, P1.5 (GND), P5.1, R1.1, R8.2, R16.2, R16.4, R16.6, R25.2, SW1.2, U1.2 (VSS), U2.2 (GND), U3.2 (GND), U4.1 (GND), U4.5 (GND), U4.10 (AGND), U4.11 (GND), U4.13 (TEST), U4.15 (GND), U4.25 (GND), U4.35 (GND), U4.47 (GND), U4.51 (GND), U4.65 (PAD), U5.4 (GND), U6.49 (PAD/GND), U7.1 (GND)
unnamed: C3.1, U2.4 (BYP)
unnamed: C11.1, U3.4 (BYP)
unnamed: C6.1, C12.1, L2.2, U4.4 (VPHY)
unnamed: C9.1, C13.1, L1.2, U4.9 (VPLL)
unnamed: C39.1, R3.2, U2.3 (EN)
unnamed: D1.A, R5.2
unnamed: D4.A, R14.1
unnamed: D5.A, R15.1
unnamed: D6.A, R17.7
unnamed: D7.A, R17.3
unnamed: D8.A, R18.1
unnamed: D9.A, R17.1
unnamed: D10.A, R17.5
unnamed: D11.4 (BA), D11.5 (GA), D11.6 (RA), J30.2
unnamed: R2.1, U1.4 (CLK), U4.62 (EECLK)
unnamed: R2.3, U1.5 (CS), U4.63 (EECS)
unnamed: R2.5, R6.2, U1.1 (DO)
unnamed: R2.8, U7.3 (OE/~ST/NC)
unnamed: R6.1, U1.3 (DI), U4.61 (EEDATA)
unnamed: R8.1, U4.6 (REF)
unnamed: R9.1, U4.14 (~RESET)

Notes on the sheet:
LED/BTN
DPair
Enable Delay ~0.001s Should enable after 1v2 rail (Test!!!)
3V3 VReg Device
~{DTR}
Break Off Section
Dual PMOD
~{DSR}
~{RI}
~{DCD}
We need the FTDI flash. We program a unique serial so multiple iCEBreakers can be used at the same time.
~{CTS}
DPair
SAO/I2C "Ear"
TXDEN
FTDI Programmer/UART/FIFO
For programming iCE
J18: Remove jumper when only programming iCE Replace jumper for programming Flash and for normal operation
RAM CS
Single PMOD
Unpopulated
iCE FPGA Flash
FPGA
For programming iCE cut traces connecting J15 and J16 pads. Short the pads 1 and 2 together of the J15 and J16 respectively. For programming Flash reverse the operations.
~{RXLED}
~{TXLED}
10k or less
1V2 VReg Device
For programming Flash
WS2812 "Ear"
RGB LED
~{RTS}

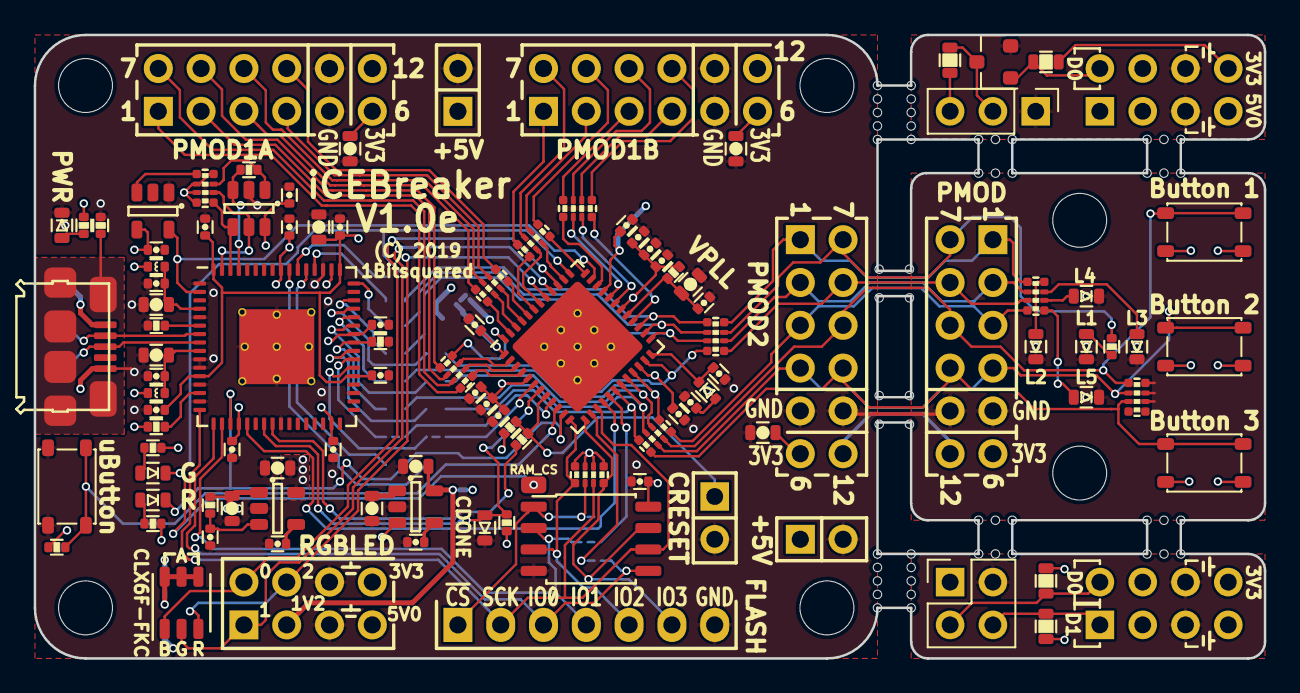
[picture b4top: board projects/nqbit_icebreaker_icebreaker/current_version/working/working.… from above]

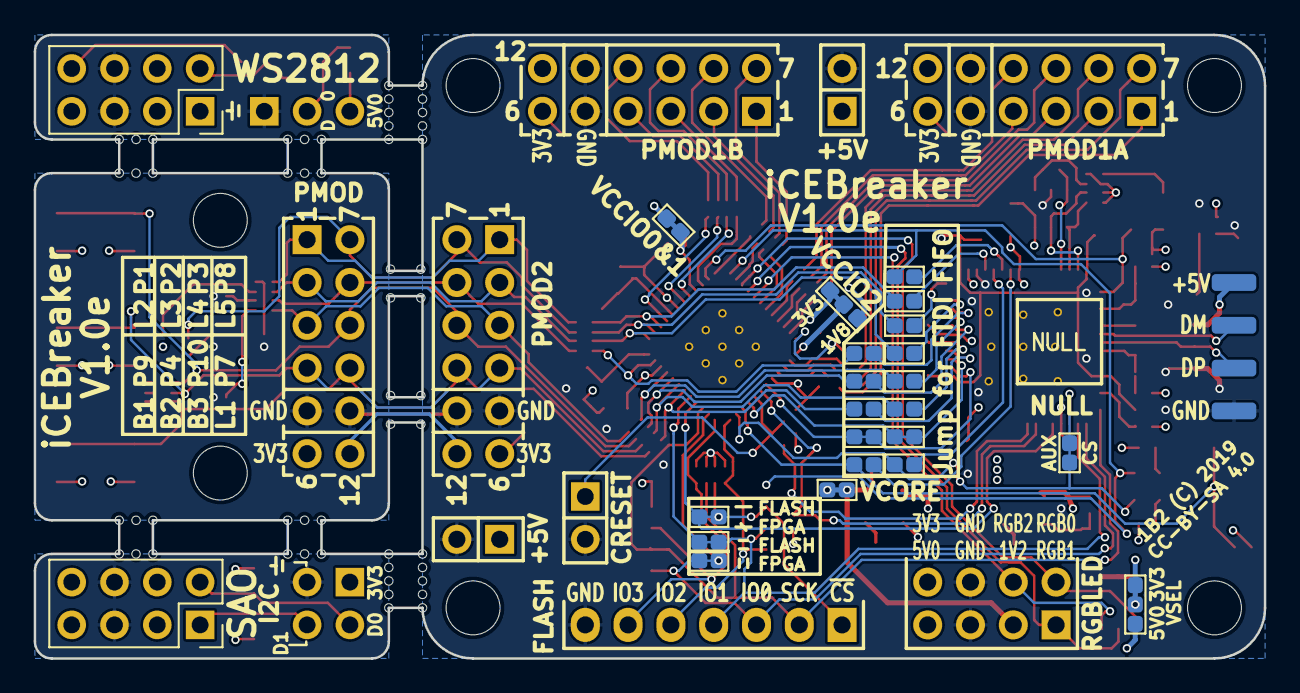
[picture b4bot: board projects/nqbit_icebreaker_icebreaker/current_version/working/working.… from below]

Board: 4 copper layers, 73.0 x 37.0 mm, 133 parts (27 on the bottom side), 126 nets.

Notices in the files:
projects/nqbit_hackrf_operacake/current_version/working/working.kicad_sch:
Copyright 2016 Great Scott Gadgets
License: GPL v2
projects/nqbit_icebreaker_icebreaker/current_version/working/working.kicad_pcb:
(C) 2019 Piotr Esden-Tempski
(C) 2019 1BitSquared
License: CC-BY-SA 4.0
1B2 (C) 2019
CC-BY-SA 4.0
(C) 2019
projects/nqbit_icebreaker_icebreaker/current_version/working/working.kicad_sch:
License: CC-BY-SA V4.0
projects/nqbit_icebreaker_icebreaker_bitsy/current_version/working/working.kicad_pcb:
(C) 2018-2020 Piotr Esden-Tempski
(C) 2018-2020 1BitSquared
CC-BY-SA
